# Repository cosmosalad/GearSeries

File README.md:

[자작 과정(kr)](https://blog.naver.com/cosmosalad/223262540878)<br/><br/>

# Gear Keyboards<br/>
All Gear series keyboards are being uploaded.

<br/><br/>

## Gear80<br/>
[▶ Check Out Gear80](https://github.com/cosmosalad/Gear80)<br/>

<p align="center">
  
</p>

<br/><br/>

## Gear60<br/>
[▶ Check Out Gear60](https://github.com/cosmosalad/Gear60)<br/>

<p align="center">
  
</p>

<br/><br/>

## Gearpad<br/>
[▶ Check Out Gearpad](https://github.com/cosmosalad/GearSeries/tree/main/Gearpad)<br/>

<p align="center">
  
</p>

<br/><br/>

## Gear40(Split Keyboard)<br/>
[▶ Check Out Gear40](https://github.com/cosmosalad/GearSeries/tree/main/Gear40)<br/>

<br/><br/>

## Gear80-M(mini Keyboard)<br/>
[▶ Check Out Gear80-M](https://github.com/cosmosalad/GearSeries/tree/main/Gear80-M)<br/>

<p align="center">

  <br/>

</p>

<p align="center">
  
</p>

<br/><br/>

## Onekey(천지인 한손키보드)<br/>
[▶ Onekey 확인](https://github.com/cosmosalad/GearSeries/tree/main/Onekey)<br/>

[▶ 전용 자판 연습 사이트](https://m.site.naver.com/1BX3V)

<br/>

- Onekey v1.0

<br/><br/>

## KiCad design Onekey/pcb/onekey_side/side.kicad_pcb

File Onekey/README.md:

[[보건복지부 국립재활원] 한손키보드 (보조기기 신청)](https://blog.naver.com/cosmosalad/223720846086)<br/><br/>

# Onekey(한손키보드)<br/>
천지인 형식 기반 한손 키보드

[▶ 전용 자판 연습 사이트](https://m.site.naver.com/1BX3V)

[▶ 키 매핑 사이트](https://vial.rocks/)

<br/>

- Onekey prototype v1.0

<br/><br/>

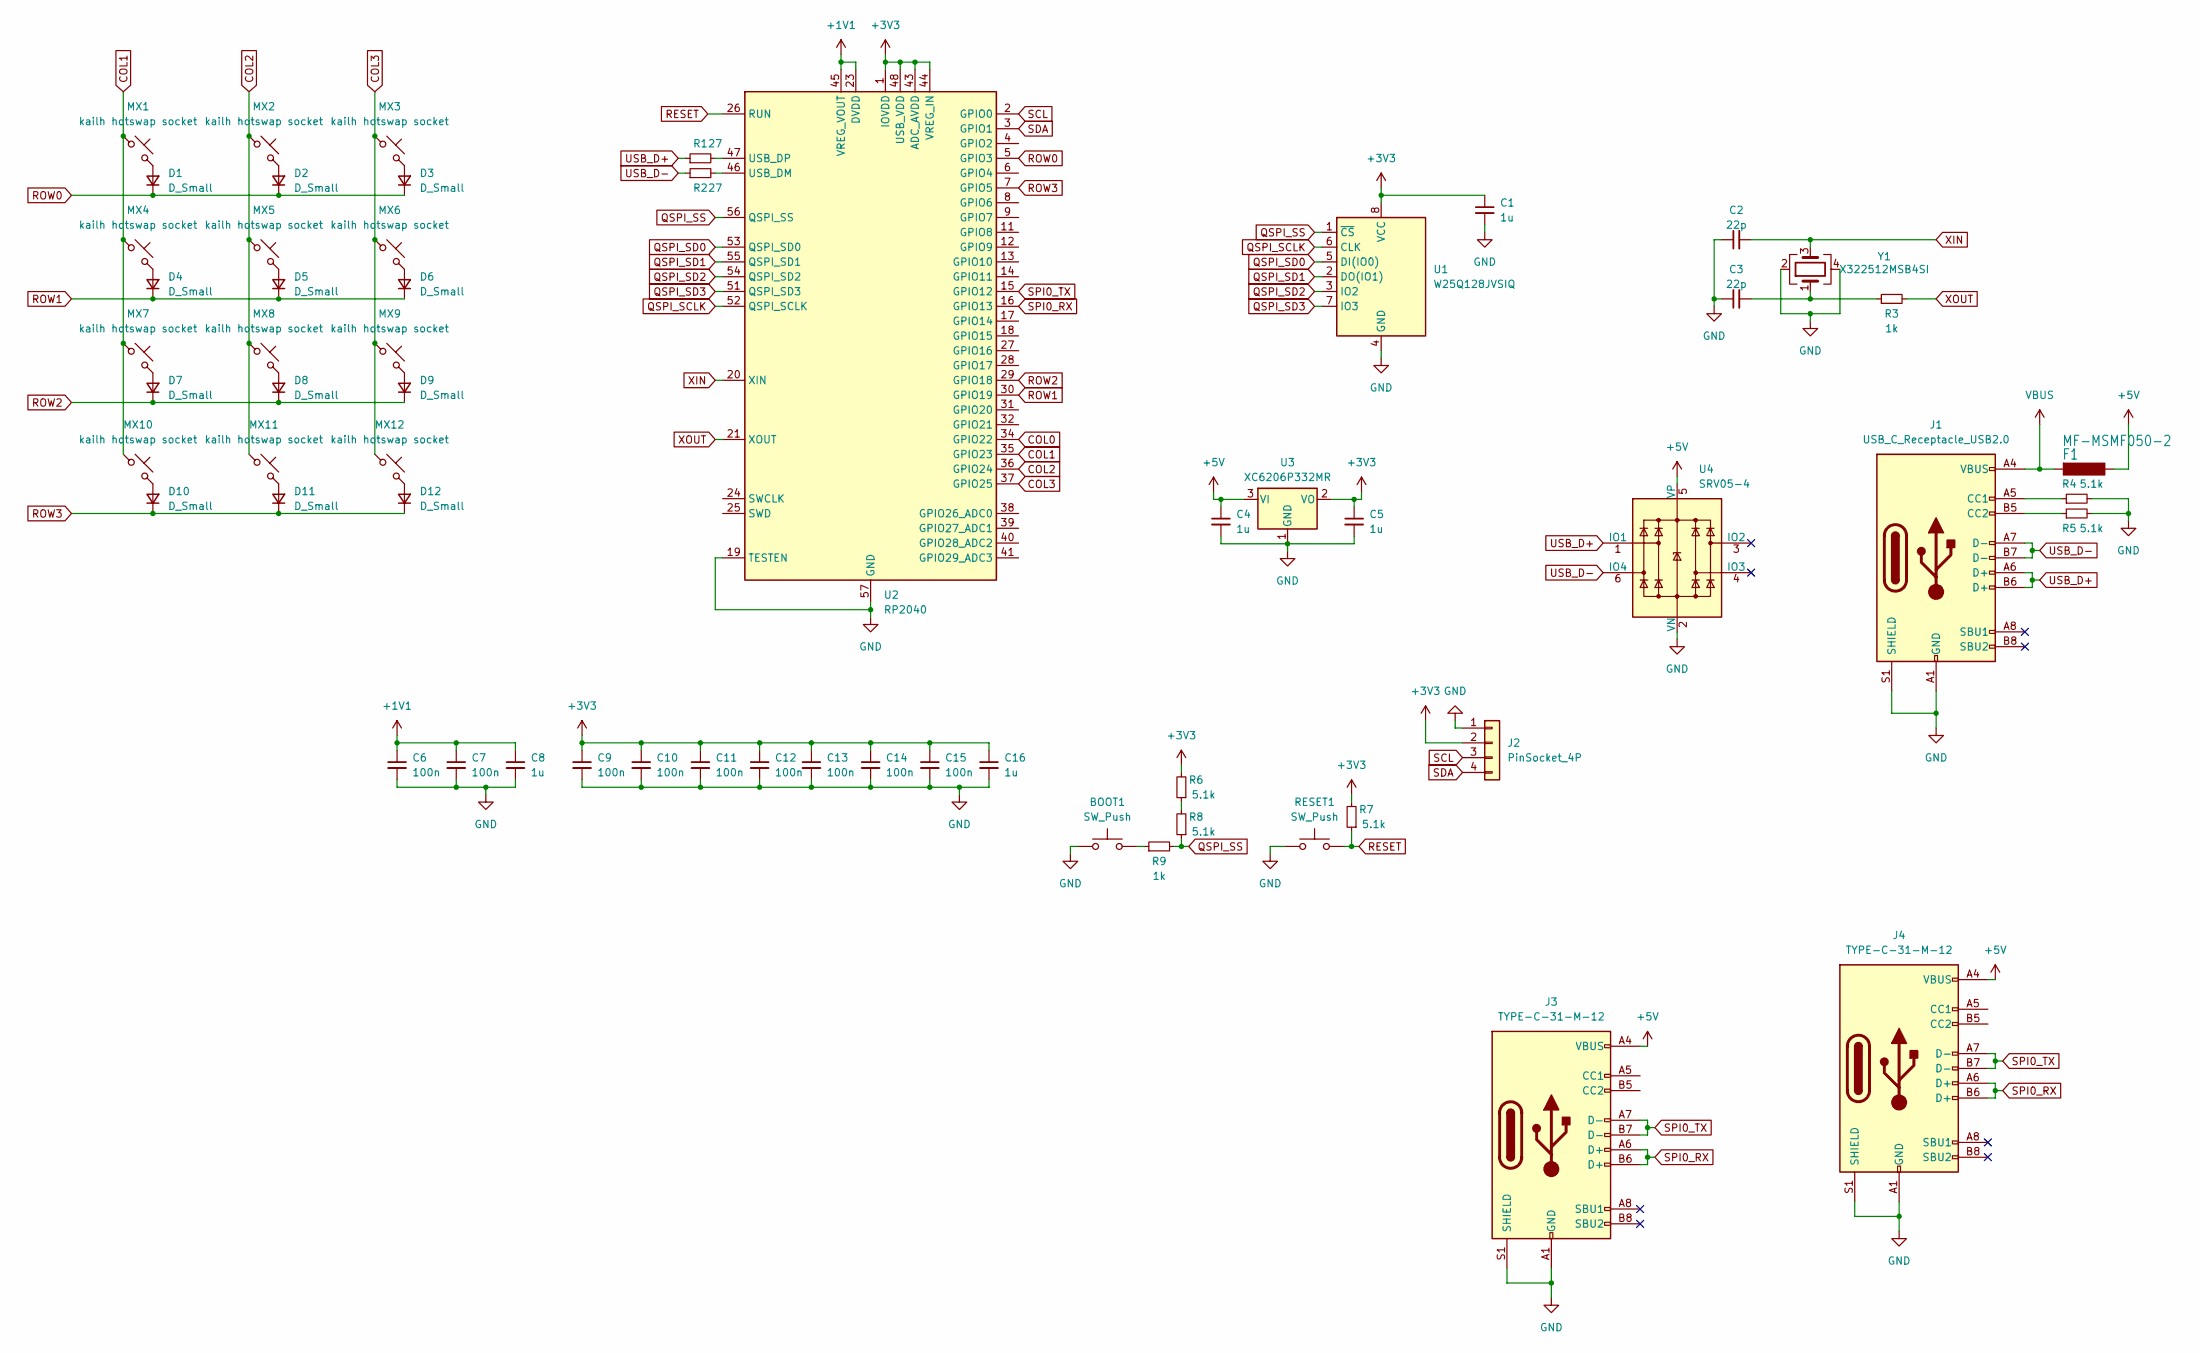
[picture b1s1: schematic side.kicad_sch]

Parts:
BOOT1: SW_Push; SW_SPST_TL3342
C1, C4, C5, C8, C16: 1u; C_0402_1005Metric
C2, C3: 22p; C_0402_1005Metric
C6, C7, C9, C10, C11, C12, C13, C14, C15: 100n; C_0402_1005Metric
D1, D2, D3, D4, D5, D6, D7, D8, D9, D10, D11, D12: D_Small; D_SOD-123
F1: MF-MSMF050-2; Fuse_1812_4532Metric
J1: USB_C_Receptacle_USB2.0; USB_C_Receptacle_HRO_TYPE-C-31-M-12
J2: PinSocket_4P; PinHeader_1x04_P2.54mm_Vertical
J3, J4: TYPE-C-31-M-12; USB_C_Receptacle_HRO_TYPE-C-31-M-12
MX1, MX2, MX3, MX4, MX5, MX6, MX7, MX8, MX9, MX10, MX11, MX12: kailh hotswap socket; SW_MX_HS_CPG151101S11_1u
R1, R2: 27; R_0402_1005Metric
R3, R9: 1k; R_0402_1005Metric
R4, R5, R6, R7, R8: 5.1k; R_0402_1005Metric
RESET1: SW_Push; SW_SPST_TL3342
U1: W25Q128JVSIQ; SOIC-8_5.23x5.23mm_P1.27mm
U2: RP2040; QFN-56-1EP_7x7mm_P0.4mm_EP3.2x3.2mm
U3: XC6206P332MR; SOT-23-3
U4: SRV05-4; SOT-23-6-routable
Y1: X322512MSB4SI; Crystal_SMD_3225-4Pin_3.2x2.5mm

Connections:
+1V1: C6.1, C7.1, C8.1, U2.23 (DVDD), U2.45 (VREG_VOUT), U2.50 (DVDD)
+3V3: C1.1, C5.1, C9.1, C10.1, C11.1, C12.1, C13.1, C14.1, C15.1, C16.1, J2.2, R6.2, R7.2, U1.8 (VCC), U2.1 (IOVDD), U2.10 (IOVDD), U2.22 (IOVDD), U2.33 (IOVDD), U2.42 (IOVDD), U2.43 (ADC_AVDD), U2.44 (VREG_IN), U2.48 (USB_VDD), U2.49 (IOVDD), U3.2 (VO)
+5V: C4.1, F1.1, J3.A4 (VBUS), J3.A9 (VBUS), J3.B4 (VBUS), J3.B9 (VBUS), J4.A4 (VBUS), J4.A9 (VBUS), J4.B4 (VBUS), J4.B9 (VBUS), U3.3 (VI), U4.5 (VP)
COL0: U2.34 (GPIO22)
COL1: MX1.1, MX4.1, MX7.1, MX10.1, U2.35 (GPIO23)
COL2: MX2.1, MX5.1, MX8.1, MX11.1, U2.36 (GPIO24)
COL3: MX3.1, MX6.1, MX9.1, MX12.1, U2.37 (GPIO25)
GND: BOOT1.1, C1.2, C2.1, C3.1, C4.2, C5.2, C6.2, C7.2, C8.2, C9.2, C10.2, C11.2, C12.2, C13.2, C14.2, C15.2, C16.2, J1.A1 (GND), J1.A12 (GND), J1.B1 (GND), J1.B12 (GND), J1.S1 (SHIELD), J2.1, J3.A1 (GND), J3.A12 (GND), J3.B1 (GND), J3.B12 (GND), J3.S1 (SHIELD), J4.A1 (GND), J4.A12 (GND), J4.B1 (GND), J4.B12 (GND), J4.S1 (SHIELD), R4.2, R5.2, RESET1.1, U1.4 (GND), U2.19 (TESTEN), U2.57 (GND), U3.1 (GND), U4.2 (VN), Y1.2, Y1.4
unnamed: BOOT1.2, R9.1
unnamed: C3.2, R3.1, Y1.1
unnamed: D1.2 (A), MX1.2
unnamed: D2.2 (A), MX2.2
unnamed: D3.2 (A), MX3.2
unnamed: D4.2 (A), MX4.2
unnamed: D5.2 (A), MX5.2
unnamed: D6.2 (A), MX6.2
unnamed: D7.2 (A), MX7.2
unnamed: D8.2 (A), MX8.2
unnamed: D9.2 (A), MX9.2
unnamed: D10.2 (A), MX10.2
unnamed: D11.2 (A), MX11.2
unnamed: D12.2 (A), MX12.2
unnamed: J1.A5 (CC1), R4.1
unnamed: J1.B5 (CC2), R5.1
unnamed: R6.1, R8.2
unnamed: R2.2, U2.46 (USB_DM)
unnamed: R1.2, U2.47 (USB_DP)
QSPI_SCLK: U1.6 (CLK), U2.52 (QSPI_SCLK)
QSPI_SD0: U1.5 (DI(IO0)), U2.53 (QSPI_SD0)
QSPI_SD1: U1.2 (DO(IO1)), U2.55 (QSPI_SD1)
QSPI_SD2: U1.3 (IO2), U2.54 (QSPI_SD2)
QSPI_SD3: U1.7 (IO3), U2.51 (QSPI_SD3)
QSPI_SS: R8.1, R9.2, U1.1 (~CS), U2.56 (QSPI_SS)
RESET: R7.1, RESET1.2, U2.26 (RUN)
ROW0: D1.1 (K), D2.1 (K), D3.1 (K), U2.5 (GPIO3)
ROW1: D4.1 (K), D5.1 (K), D6.1 (K), U2.30 (GPIO19)
ROW2: D7.1 (K), D8.1 (K), D9.1 (K), U2.29 (GPIO18)
ROW3: D10.1 (K), D11.1 (K), D12.1 (K), U2.7 (GPIO5)
SCL: J2.3, U2.2 (GPIO0)
SDA: J2.4, U2.3 (GPIO1)
SPI0_RX: J3.A6 (D+), J3.B6 (D+), J4.A6 (D+), J4.B6 (D+), U2.16 (GPIO13)
SPI0_TX: J3.A7 (D-), J3.B7 (D-), J4.A7 (D-), J4.B7 (D-), U2.15 (GPIO12)
USB_D+: J1.A6 (D+), J1.B6 (D+), R1.1, U4.1 (IO1)
USB_D-: J1.A7 (D-), J1.B7 (D-), R2.1, U4.6 (IO4)
VBUS: F1.2, J1.A4 (VBUS), J1.A9 (VBUS), J1.B4 (VBUS), J1.B9 (VBUS)
XIN: C2.2, U2.20 (XIN), Y1.3
XOUT: R3.2, U2.21 (XOUT)

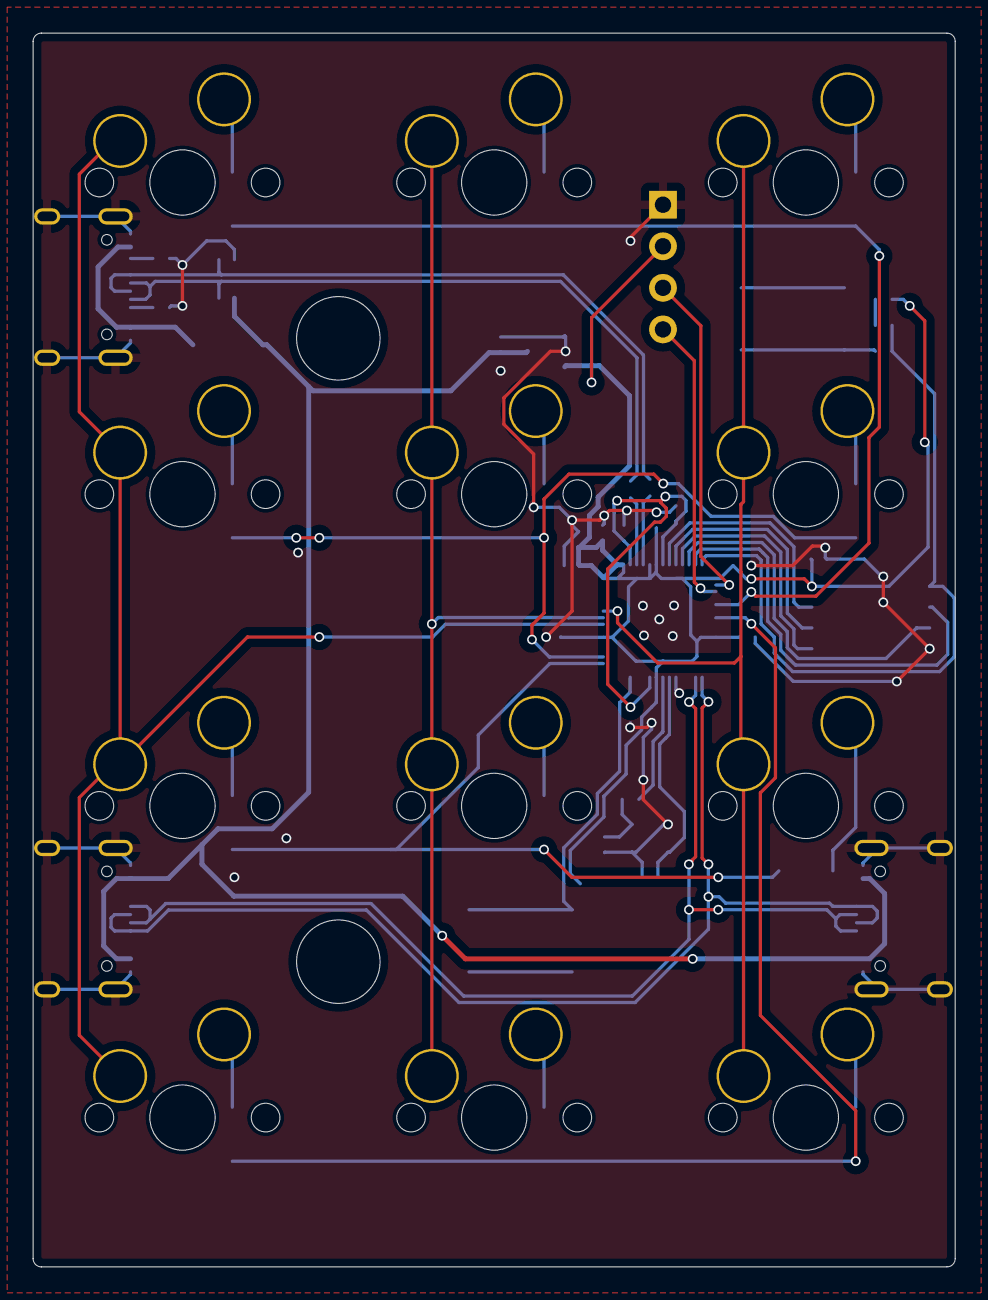
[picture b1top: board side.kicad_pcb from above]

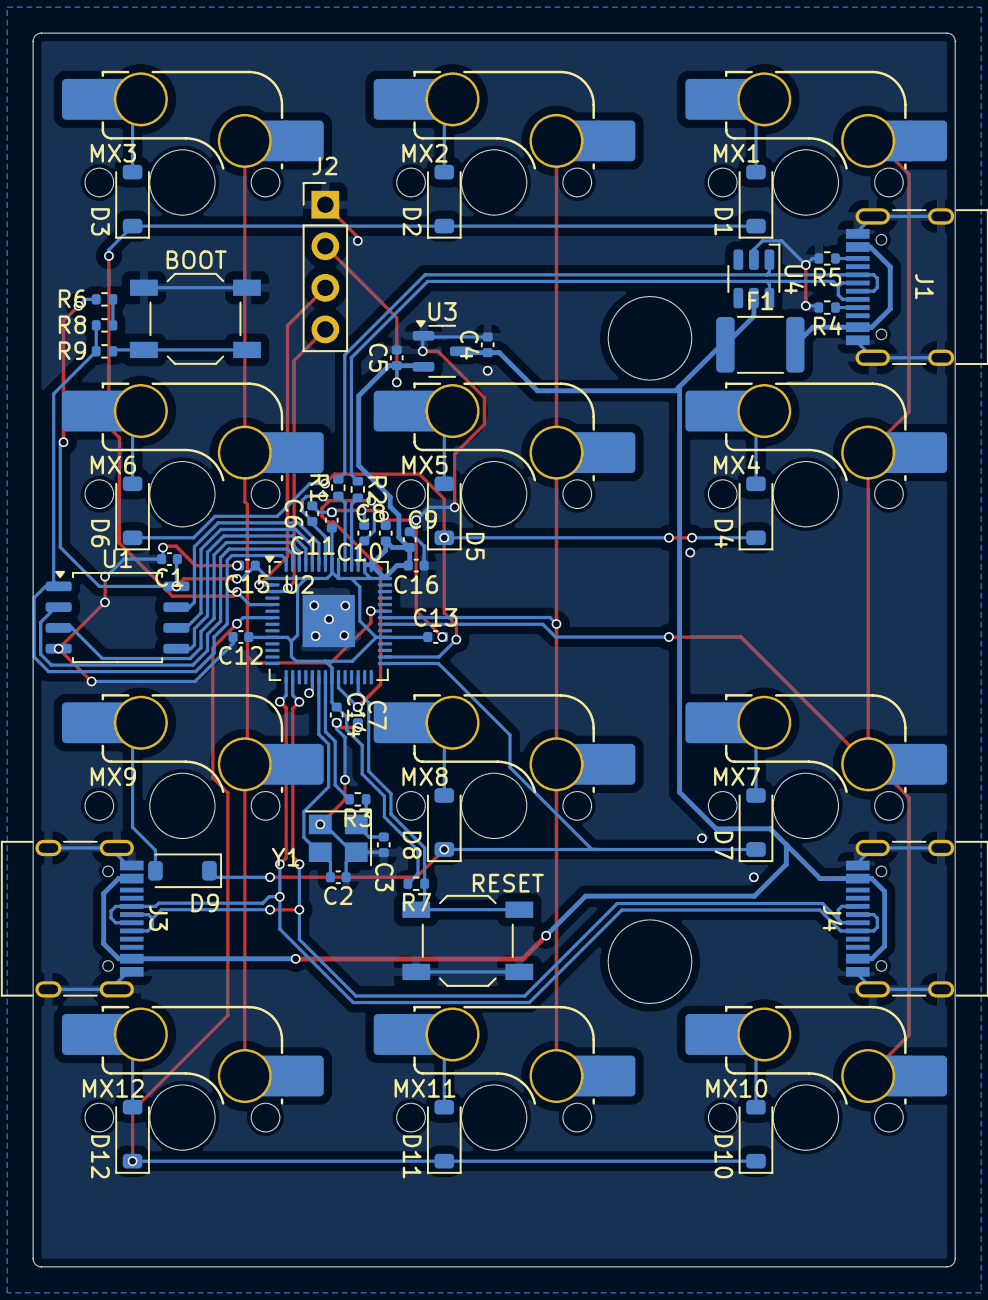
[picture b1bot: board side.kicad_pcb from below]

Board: 2 copper layers, 56.4 x 75.4 mm, 61 parts (61 on the bottom side), 46 nets.

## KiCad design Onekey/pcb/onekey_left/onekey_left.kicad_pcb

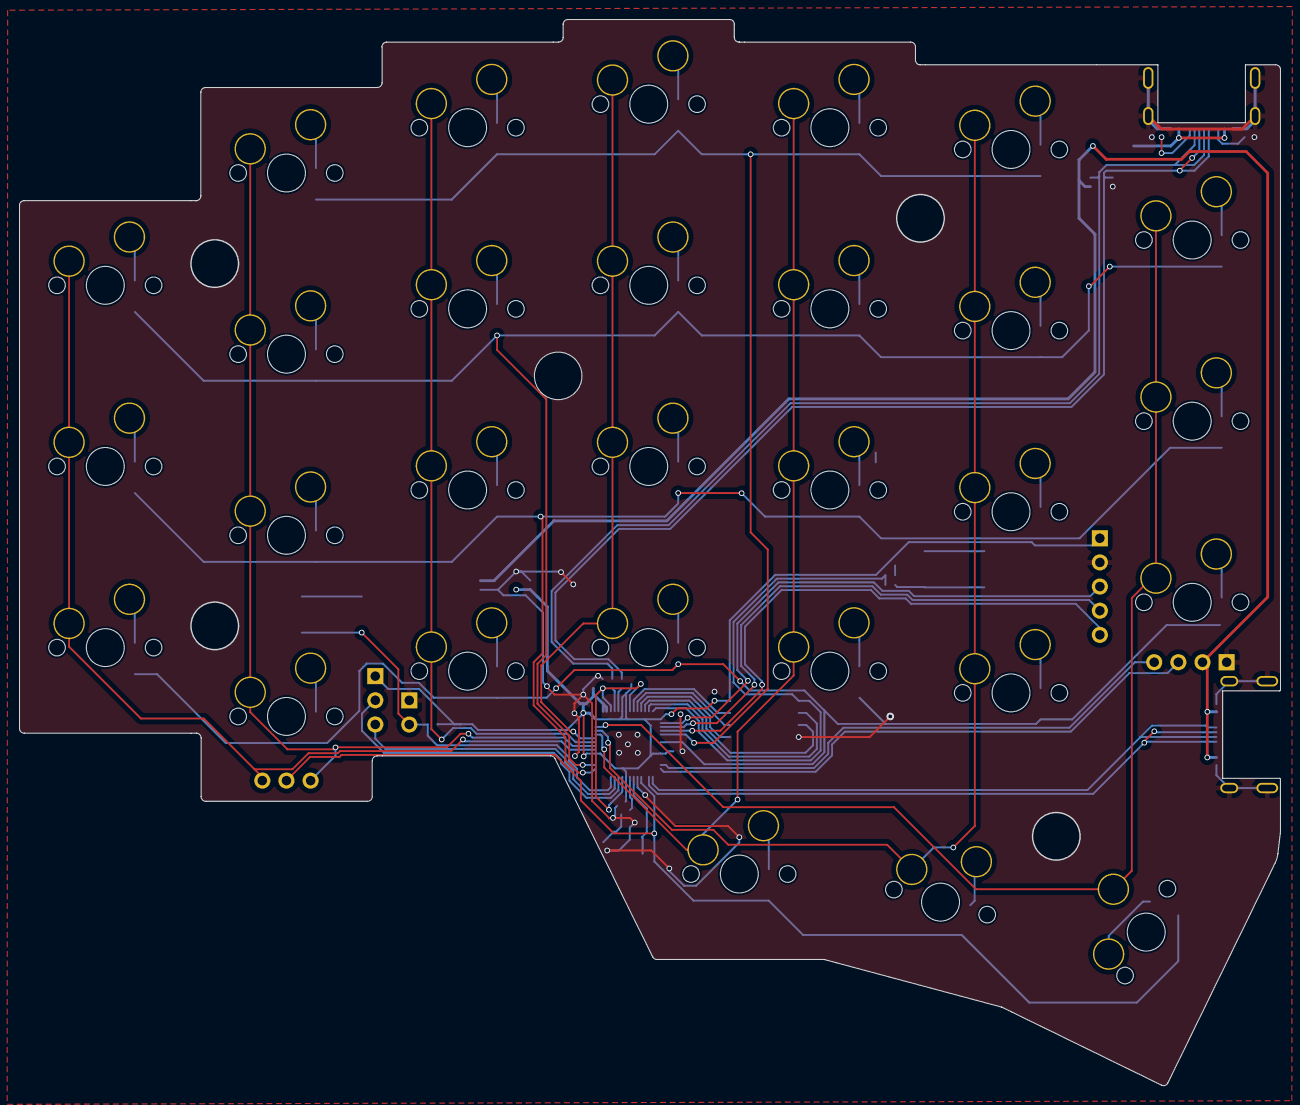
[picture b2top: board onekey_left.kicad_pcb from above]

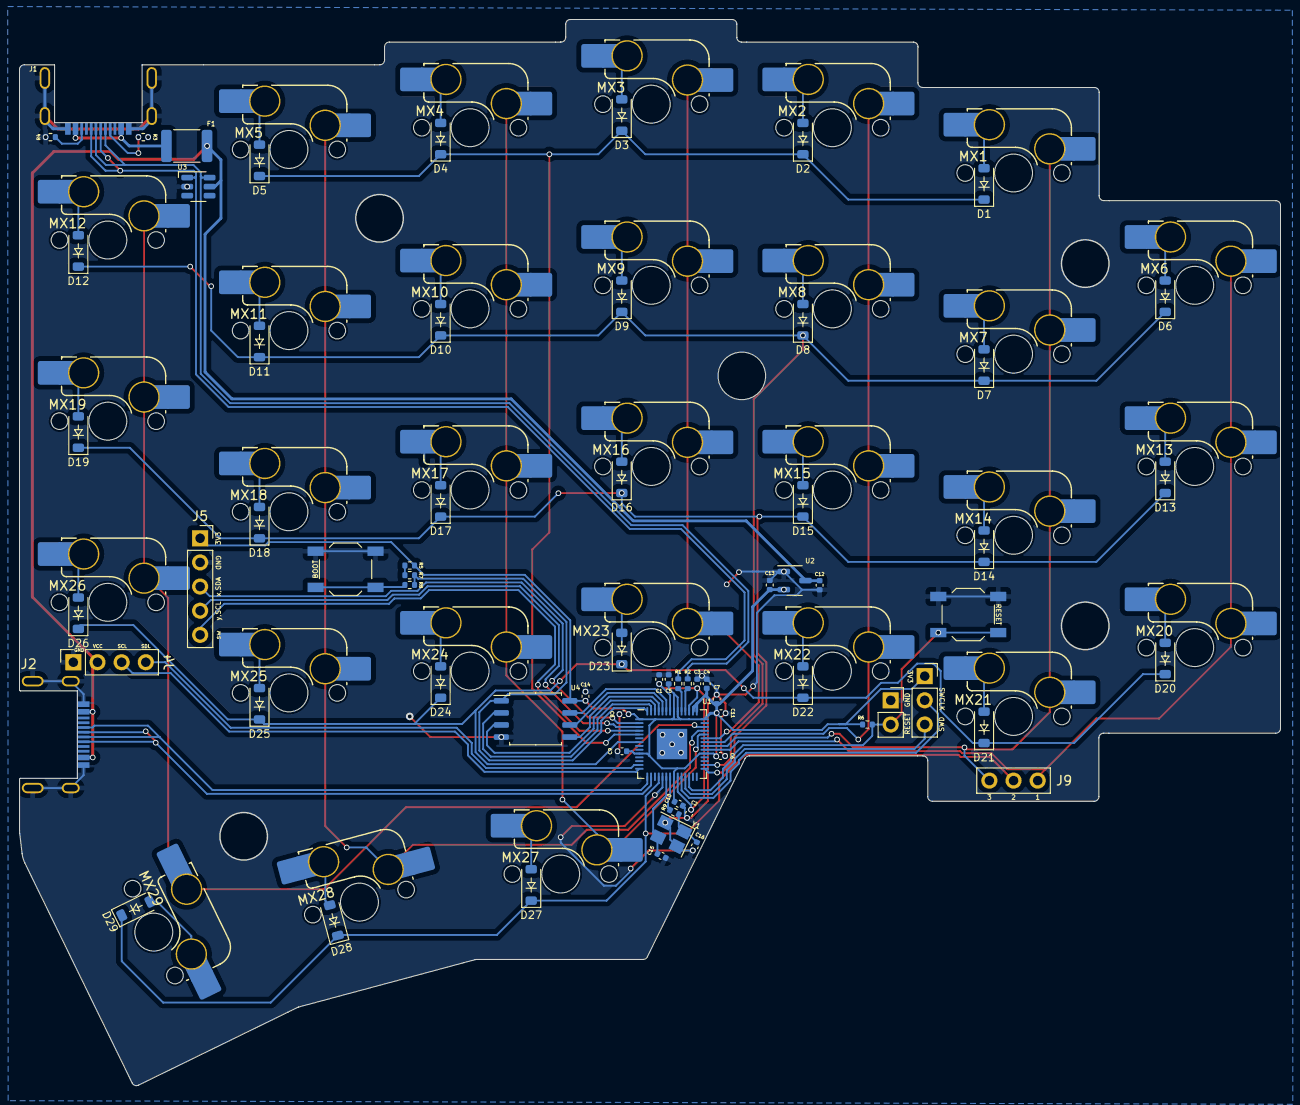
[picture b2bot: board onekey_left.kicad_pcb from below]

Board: 2 copper layers, 132.6 x 112.1 mm, 98 parts (96 on the bottom side), 73 nets.

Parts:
BOOT1: SW_Push; SW_SPST_TL3342
C1, C2, C4, C5, C6, C7, C8, C9, C10: 100n; C_0402_1005Metric
C3, C11, C12, C13, C14: 1u; C_0402_1005Metric
C15, C16: 22p; C_0402_1005Metric
D1, D2, D3, D4, D5, D6, D7, D8, D9, D10, D11, D12, D13, D14, D15, D16, D17, D18, D19, D20, D21, D22, D23, D24, D25, D26, D27, D28, D29: D_Small; D_SOD-123_new
F1: MF-MSMF050-2; Fuse_1812_4532Metric
J1, J2: TYPE-C-31-M-13; HRO-TYPE-C-31-M-13
J3: SWD_PinSocket; PinSocket_1x03_P2.54mm_Vertical
J4: PinSocket_4P; PinHeader_1x04_P2.54mm_Vertical
J5: PinSocket_5P; PinHeader_1x05_P2.54mm_Vertical
J9: side_b_PinSocket; PinSocket_1x03_P2.54mm_Vertical
MX1, MX2, MX3, MX4, MX5, MX6, MX7, MX8, MX9, MX10, MX11, MX12, MX13, MX14, MX15, MX16, MX17, MX18, MX19, MX20, MX21, MX22, MX23, MX24, MX25, MX26, MX27, MX28: kailh hotswap socket; SW_MX_HS_1u
MX29: kailh hotswap socket; SW_MX_HS_1.5u
R1, R2: 27; R_0402_1005Metric
R3, R4, R5, R6, R7: 5.1k; R_0402_1005Metric
R8, R9: 1k; R_0402_1005Metric
RESET1: PinSocket_2P; PinSocket_1x02_P2.54mm_Vertical
RESET2: SW_Push; SW_SPST_TL3342
U1: RP2040; QFN-56-1EP_7x7mm_P0.4mm_EP3.2x3.2mm
U2: XC6206P332MR; SOT-23-3
U3: SRV05-4; SOT-23-6-routable
U4: W25Q128JVSIQ; SOIC-8_5.23x5.23mm_P1.27mm
Y1: X322512MSB4SI; Crystal_SMD_3225-4Pin_3.2x2.5mm

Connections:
+1V1L: C1.1, C2.1, C3.1, U1.23 (DVDD), U1.45 (VREG_VOUT), U1.50 (DVDD)
+3V3L: C4.1, C5.1, C6.1, C7.1, C8.1, C9.1, C10.1, C11.1, C13.1, C14.1, J3.1, J5.1, R5.2, R6.2, U1.1 (IOVDD), U1.10 (IOVDD), U1.22 (IOVDD), U1.33 (IOVDD), U1.42 (IOVDD), U1.43 (ADC_AVDD), U1.44 (VREG_IN), U1.48 (USB_VDD), U1.49 (IOVDD), U2.2 (VO), U4.8 (VCC)
+5VL: C12.1, F1.1, J2.A4 (VBUS), J2.A9 (VBUS), J2.B4 (VBUS), J2.B9 (VBUS), J4.2, U2.3 (VI), U3.5 (VP)
COL0_L: J9.1, MX6.1, MX13.1, MX20.1, U1.34 (GPIO22)
COL1_L: J9.3, MX1.1, MX7.1, MX14.1, MX21.1, U1.35 (GPIO23)
COL2_L: MX2.1, MX8.1, MX15.1, MX22.1, U1.36 (GPIO24)
COL3_L: MX3.1, MX9.1, MX16.1, MX23.1, U1.37 (GPIO25)
COL4_L: MX4.1, MX10.1, MX17.1, MX24.1, MX27.1, U1.38 (GPIO26_ADC0)
COL5_L: MX5.1, MX11.1, MX18.1, MX25.1, MX28.1, U1.39 (GPIO27_ADC1)
COL6_L: MX12.1, MX19.1, MX26.1, MX29.2, U1.40 (GPIO28_ADC2)
GNDL: BOOT1.1, C1.2, C2.2, C3.2, C4.2, C5.2, C6.2, C7.2, C8.2, C9.2, C10.2, C11.2, C12.2, C13.2, C14.2, C15.1, C16.1, J1.A1 (GND), J1.A12 (GND), J1.B1 (GND), J1.B12 (GND), J1.S1 (SHIELD), J2.A1 (GND), J2.A12 (GND), J2.B1 (GND), J2.B12 (GND), J2.S1 (SHIELD), J4.1, J5.2, R3.2, R4.2, RESET1.1, RESET2.1, U1.19 (TESTEN), U1.57 (GND), U2.1 (GND), U3.2 (VN), U4.4 (GND), Y1.2, Y1.4
unnamed: BOOT1.2, R8.1
unnamed: C16.2, R9.1, Y1.1
unnamed: D1.2 (A), MX1.2
unnamed: D2.2 (A), MX2.2
unnamed: D3.2 (A), MX3.2
unnamed: D4.2 (A), MX4.2
unnamed: D5.2 (A), MX5.2
unnamed: D6.2 (A), MX6.2
unnamed: D7.2 (A), MX7.2
unnamed: D8.2 (A), MX8.2
unnamed: D9.2 (A), MX9.2
unnamed: D10.2 (A), MX10.2
unnamed: D11.2 (A), MX11.2
unnamed: D12.2 (A), MX12.2
unnamed: D13.2 (A), MX13.2
unnamed: D14.2 (A), MX14.2
unnamed: D15.2 (A), MX15.2
unnamed: D16.2 (A), MX16.2
unnamed: D17.2 (A), MX17.2
unnamed: D18.2 (A), MX18.2
unnamed: D19.2 (A), MX19.2
unnamed: D20.2 (A), MX20.2
unnamed: D21.2 (A), MX21.2
unnamed: D22.2 (A), MX22.2
unnamed: D23.2 (A), MX23.2
unnamed: D24.2 (A), MX24.2
unnamed: D25.2 (A), MX25.2
unnamed: D26.2 (A), MX26.2
unnamed: D27.2 (A), MX27.2
unnamed: D28.2 (A), MX28.2
unnamed: D29.2 (A), MX29.1
unnamed: J1.A5 (CC1), R3.1
unnamed: J1.B5 (CC2), R4.1
unnamed: R5.1, R7.2
unnamed: R2.2, U1.46 (USB_DM)
unnamed: R1.2, U1.47 (USB_DP)
QSPI_SCLK_L: U1.52 (QSPI_SCLK), U4.6 (CLK)
QSPI_SD0_L: U1.53 (QSPI_SD0), U4.5 (DI(IO0))
QSPI_SD1_L: U1.55 (QSPI_SD1), U4.2 (DO(IO1))
QSPI_SD2_L: U1.54 (QSPI_SD2), U4.3 (IO2)
QSPI_SD3_L: U1.51 (QSPI_SD3), U4.7 (IO3)
QSPI_SS_L: R7.1, R8.2, U1.56 (QSPI_SS), U4.1 (~CS)
RESET_L: R6.1, RESET1.2, RESET2.2, U1.26 (RUN)
ROW0_L: D1.1 (K), D2.1 (K), D3.1 (K), D4.1 (K), D5.1 (K), U1.5 (GPIO3)
ROW1_L: D6.1 (K), D7.1 (K), D8.1 (K), D9.1 (K), D10.1 (K), D11.1 (K), D12.1 (K), U1.30 (GPIO19)
ROW2_L: D13.1 (K), D14.1 (K), D15.1 (K), D16.1 (K), D17.1 (K), D18.1 (K), D19.1 (K), U1.29 (GPIO18)
ROW3_L: D20.1 (K), D21.1 (K), D22.1 (K), D23.1 (K), D24.1 (K), D25.1 (K), D26.1 (K), U1.7 (GPIO5)
ROW4_L: D27.1 (K), D28.1 (K), D29.1 (K), J9.2, U1.18 (GPIO15)
SCL_L: J4.3, U1.14 (GPIO11)
SDA_L: J4.4, U1.13 (GPIO10)
SPI0_RX_L: J2.A6 (D+), J2.B6 (D+), U1.16 (GPIO13)
SPI0_TX_L: J2.A7 (D-), J2.B7 (D-), U1.15 (GPIO12)
SWCLK_L: J3.2, U1.24 (SWCLK)
SWD_L: J3.3, U1.25 (SWD)
USB_D+_L: J1.A6 (D+), J1.B6 (D+), R1.1, U3.1 (IO1)
USB_D-_L: J1.A7 (D-), J1.B7 (D-), R2.1, U3.6 (IO4)
VBUSL: F1.2, J1.A4 (VBUS), J1.A9 (VBUS), J1.B4 (VBUS), J1.B9 (VBUS)
XIN_L: C15.2, U1.20 (XIN), Y1.3
XOUT_L: R9.2, U1.21 (XOUT)
sw_L: J5.5, U1.4 (GPIO2)
vrx_L: J5.3, U1.2 (GPIO0)
vry_L: J5.4, U1.3 (GPIO1)

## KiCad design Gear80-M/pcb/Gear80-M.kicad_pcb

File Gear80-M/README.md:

[자작 과정(kr)](https://blog.naver.com/cosmosalad/223262540878)<br/><br/>

# Gear80-M(mini keyboad)<br/>
Gear80-M is a mini keyboard based on STM32F072C8T

<br/>

- gear80-M

<p align="center">

  <br/>

</p>

<p align="center">
  
</p>

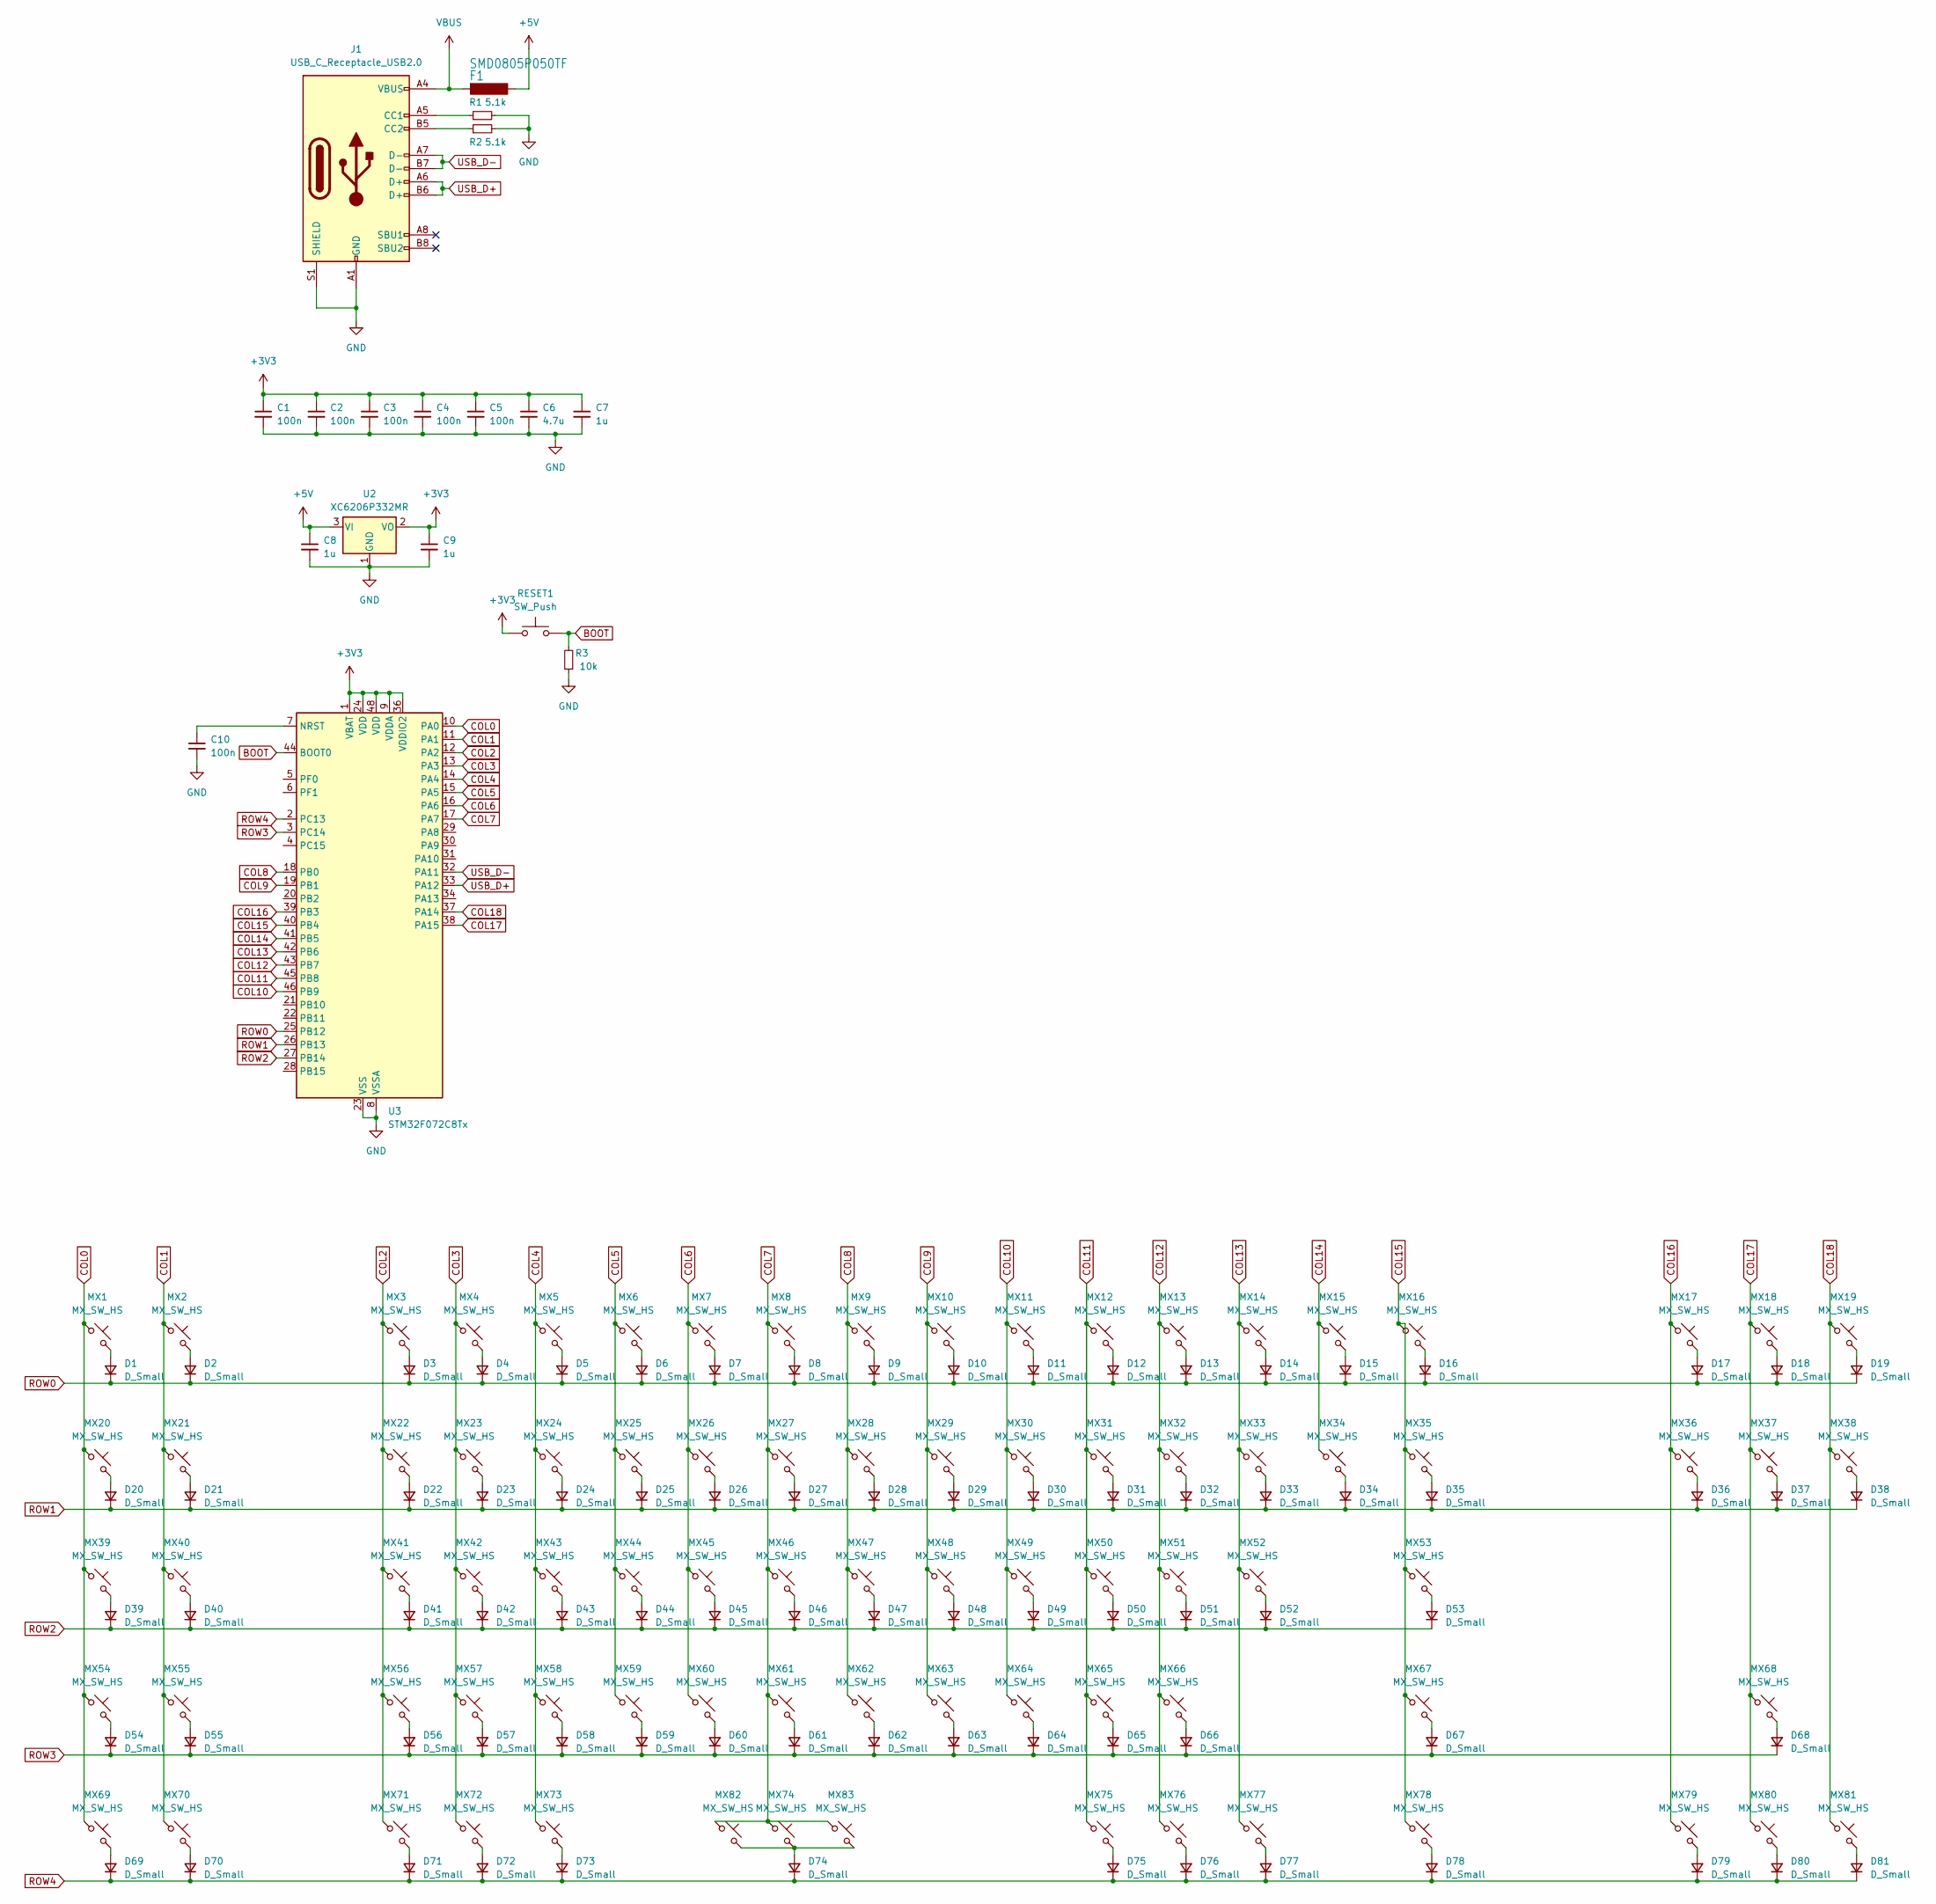
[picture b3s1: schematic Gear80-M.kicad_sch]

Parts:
C1, C2, C3, C4, C5, C10: 100n; C_0402_1005Metric
C6: 4.7u; C_0402_1005Metric
C7, C8, C9: 1u; C_0402_1005Metric
D1, D2, D3, D4, D5, D6, D7, D8, D9, D10, D11, D12, D13, D14, D15, D16, D17, D18, D19, D20, D21, D22, D23, D24, D25, D26, D27, D28, D29, D30, D31, D32, D33, D34, D35, D36, D37, D38, D39, D40, D41, D42, D43, D44, D45, D46, D47, D48, D49, D50, D51, D52, D53, D54, D55, D56, D57, D58, D59, D60, D61, D62, D63, D64, D65, D66, D67, D68, D69, D70, D71, D72, D73, D74, D75, D76, D77, D78, D79, D80, D81: D_Small; D_SOD-323_new
F1: SMD0805P050TF; R_0805_2012Metric
J1: USB_C_Receptacle_USB2.0; USB_C_Receptacle_GCT_USB4110
MX1, MX2, MX3, MX4, MX5, MX6, MX7, MX8, MX9, MX10, MX11, MX12, MX13, MX14, MX15, MX16, MX17, MX18, MX19, MX20, MX21, MX22, MX23, MX24, MX25, MX26, MX27, MX28, MX29, MX30, MX31, MX32, MX33, MX34, MX35, MX36, MX37, MX38, MX39, MX40, MX41, MX42, MX43, MX44, MX45, MX46, MX47, MX48, MX49, MX50, MX51, MX52, MX53, MX54, MX55, MX56, MX57, MX58, MX59, MX60, MX61, MX62, MX63, MX64, MX65, MX66, MX67, MX68, MX69, MX70, MX71, MX72, MX73, MX74, MX75, MX76, MX77, MX78, MX79, MX80, MX81, MX82, MX83: MX_SW_HS; PinSocket_1x02_P2.54mm_Vertical_new_qmk
R1, R2: 5.1k; R_0402_1005Metric
R3: 10k; R_0402_1005Metric
RESET1: SW_Push; reset1
U2: XC6206P332MR; SOT-23-3
U3: STM32F072C8Tx; LQFP-48_7x7mm_P0.5mm

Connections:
+3V3: C1.1, C2.1, C3.1, C4.1, C5.1, C6.1, C7.1, C9.1, RESET1.1, U2.2 (VO), U3.1 (VBAT), U3.9 (VDDA), U3.24 (VDD), U3.36 (VDDIO2), U3.48 (VDD)
+5V: C8.1, F1.1, U2.3 (VI)
BOOT: R3.2, RESET1.2, U3.44 (BOOT0)
COL0: MX1.1, MX20.1, MX39.1, MX54.1, MX69.1, U3.10 (PA0)
COL1: MX2.1, MX21.1, MX40.1, MX55.1, MX70.1, U3.11 (PA1)
COL2: MX3.1, MX22.1, MX41.1, MX56.1, MX71.1, U3.12 (PA2)
COL3: MX4.1, MX23.1, MX42.1, MX57.1, MX72.1, U3.13 (PA3)
COL4: MX5.1, MX24.1, MX43.1, MX58.1, MX73.1, U3.14 (PA4)
COL5: MX6.1, MX25.1, MX44.1, MX59.1, U3.15 (PA5)
COL6: MX7.1, MX26.1, MX45.1, MX60.1, U3.16 (PA6)
COL7: MX8.1, MX27.1, MX46.1, MX61.1, MX74.1, MX82.1, MX83.1, U3.17 (PA7)
COL8: MX9.1, MX28.1, MX47.1, MX62.1, U3.18 (PB0)
COL9: MX10.1, MX29.1, MX48.1, MX63.1, U3.19 (PB1)
COL10: MX11.1, MX30.1, MX49.1, MX64.1, U3.46 (PB9)
COL11: MX12.1, MX31.1, MX50.1, MX65.1, MX75.1, U3.45 (PB8)
COL12: MX13.1, MX32.1, MX51.1, MX66.1, MX76.1, U3.43 (PB7)
COL13: MX14.1, MX33.1, MX52.1, MX77.1, U3.42 (PB6)
COL14: MX15.1, MX34.1, U3.41 (PB5)
COL15: MX16.1, MX35.1, MX53.1, MX67.1, MX78.1, U3.40 (PB4)
COL16: MX17.1, MX36.1, MX79.1, U3.39 (PB3)
COL17: MX18.1, MX37.1, MX68.1, MX80.1, U3.38 (PA15)
COL18: MX19.1, MX38.1, MX81.1, U3.37 (PA14)
GND: C1.2, C2.2, C3.2, C4.2, C5.2, C6.2, C7.2, C8.2, C9.2, C10.2, J1.A1 (GND), J1.A12 (GND), J1.B1 (GND), J1.B12 (GND), J1.S1 (SHIELD), R1.2, R2.2, R3.1, U2.1 (GND), U3.8 (VSSA), U3.23 (VSS), U3.35 (VSS), U3.47 (VSS)
unnamed: D1.2 (A), MX1.2
unnamed: D2.2 (A), MX2.2
unnamed: D3.2 (A), MX3.2
unnamed: D4.2 (A), MX4.2
unnamed: D5.2 (A), MX5.2
unnamed: D6.2 (A), MX6.2
unnamed: D7.2 (A), MX7.2
unnamed: D8.2 (A), MX8.2
unnamed: D9.2 (A), MX9.2
unnamed: D10.2 (A), MX10.2
unnamed: D11.2 (A), MX11.2
unnamed: D12.2 (A), MX12.2
unnamed: D13.2 (A), MX13.2
unnamed: D14.2 (A), MX14.2
unnamed: D15.2 (A), MX15.2
unnamed: D16.2 (A), MX16.2
unnamed: D17.2 (A), MX17.2
unnamed: D18.2 (A), MX18.2
unnamed: D19.2 (A), MX19.2
unnamed: D20.2 (A), MX20.2
unnamed: D21.2 (A), MX21.2
unnamed: D22.2 (A), MX22.2
unnamed: D23.2 (A), MX23.2
unnamed: D24.2 (A), MX24.2
unnamed: D25.2 (A), MX25.2
unnamed: D26.2 (A), MX26.2
unnamed: D27.2 (A), MX27.2
unnamed: D28.2 (A), MX28.2
unnamed: D29.2 (A), MX29.2
unnamed: D30.2 (A), MX30.2
unnamed: D31.2 (A), MX31.2
unnamed: D32.2 (A), MX32.2
unnamed: D33.2 (A), MX33.2
unnamed: D34.2 (A), MX34.2
unnamed: D35.2 (A), MX35.2
unnamed: D36.2 (A), MX36.2
unnamed: D37.2 (A), MX37.2
unnamed: D38.2 (A), MX38.2
unnamed: D39.2 (A), MX39.2
unnamed: D40.2 (A), MX40.2
unnamed: D41.2 (A), MX41.2
unnamed: D42.2 (A), MX42.2
unnamed: D43.2 (A), MX43.2
unnamed: D44.2 (A), MX44.2
unnamed: D45.2 (A), MX45.2
unnamed: D46.2 (A), MX46.2
unnamed: D47.2 (A), MX47.2
unnamed: D48.2 (A), MX48.2
unnamed: D49.2 (A), MX49.2
unnamed: D50.2 (A), MX50.2
unnamed: D51.2 (A), MX51.2
unnamed: D52.2 (A), MX52.2
unnamed: D53.2 (A), MX53.2
unnamed: D54.2 (A), MX54.2
unnamed: D55.2 (A), MX55.2
unnamed: D56.2 (A), MX56.2
unnamed: D57.2 (A), MX57.2
unnamed: D58.2 (A), MX58.2
unnamed: D59.2 (A), MX59.2
unnamed: D60.2 (A), MX60.2
unnamed: D61.2 (A), MX61.2
unnamed: D62.2 (A), MX62.2
unnamed: D63.2 (A), MX63.2
unnamed: D64.2 (A), MX64.2
unnamed: D65.2 (A), MX65.2
unnamed: D66.2 (A), MX66.2
unnamed: D67.2 (A), MX67.2
unnamed: D68.2 (A), MX68.2
unnamed: D69.2 (A), MX69.2
unnamed: D70.2 (A), MX70.2
unnamed: D71.2 (A), MX71.2
unnamed: D72.2 (A), MX72.2
unnamed: D73.2 (A), MX73.2
unnamed: D74.2 (A), MX74.2, MX82.2, MX83.2
unnamed: D75.2 (A), MX75.2
unnamed: D76.2 (A), MX76.2
unnamed: D77.2 (A), MX77.2
unnamed: D78.2 (A), MX78.2
unnamed: D79.2 (A), MX79.2
unnamed: D80.2 (A), MX80.2
unnamed: D81.2 (A), MX81.2
unnamed: J1.A5 (CC1), R1.1
unnamed: J1.B5 (CC2), R2.1
unnamed: C10.1, U3.7 (NRST)
ROW0: D1.1 (K), D2.1 (K), D3.1 (K), D4.1 (K), D5.1 (K), D6.1 (K), D7.1 (K), D8.1 (K), D9.1 (K), D10.1 (K), D11.1 (K), D12.1 (K), D13.1 (K), D14.1 (K), D15.1 (K), D16.1 (K), D17.1 (K), D18.1 (K), D19.1 (K), U3.25 (PB12)
ROW1: D20.1 (K), D21.1 (K), D22.1 (K), D23.1 (K), D24.1 (K), D25.1 (K), D26.1 (K), D27.1 (K), D28.1 (K), D29.1 (K), D30.1 (K), D31.1 (K), D32.1 (K), D33.1 (K), D34.1 (K), D35.1 (K), D36.1 (K), D37.1 (K), D38.1 (K), U3.26 (PB13)
ROW2: D39.1 (K), D40.1 (K), D41.1 (K), D42.1 (K), D43.1 (K), D44.1 (K), D45.1 (K), D46.1 (K), D47.1 (K), D48.1 (K), D49.1 (K), D50.1 (K), D51.1 (K), D52.1 (K), D53.1 (K), U3.27 (PB14)
ROW3: D54.1 (K), D55.1 (K), D56.1 (K), D57.1 (K), D58.1 (K), D59.1 (K), D60.1 (K), D61.1 (K), D62.1 (K), D63.1 (K), D64.1 (K), D65.1 (K), D66.1 (K), D67.1 (K), D68.1 (K), U3.3 (PC14)
ROW4: D69.1 (K), D70.1 (K), D71.1 (K), D72.1 (K), D73.1 (K), D74.1 (K), D75.1 (K), D76.1 (K), D77.1 (K), D78.1 (K), D79.1 (K), D80.1 (K), D81.1 (K), U3.2 (PC13)
USB_D+: J1.A6 (D+), J1.B6 (D+), U3.33 (PA12)
USB_D-: J1.A7 (D-), J1.B7 (D-), U3.32 (PA11)
VBUS: F1.2, J1.A4 (VBUS), J1.A9 (VBUS), J1.B4 (VBUS), J1.B9 (VBUS)
